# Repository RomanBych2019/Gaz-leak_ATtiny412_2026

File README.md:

# Контроллер датчика газа на ATtiny412

Назначение выводов:

- PA0: UPDI
- PA1: светодиод состояния платы
- PA2: вход АЦП датчика с внешней подтяжкой 4.7 кОм к GND
- PA3: отладочный TX, программный UART 2400 бод
- PA6: выход силового ключа 2
- PA7: выход силового ключа 1

Основная логика:

- после прогрева выполняется первоначальная калибровка чистого воздуха;
- новое значение сравнивается с сохраненным в EEPROM: если разница не больше допустимой, оно применяется и записывается; если разница большая, используется сохраненное значение;
- обрыв датчика или замыкание линии на GND определяется по АЦП около 0 В;
- замыкание выхода датчика на питание определяется по АЦП около +5 В;
- в LIN-варианте PA7 управляет BTS4142N; программная проверка замыкания нагрузки и повторные включения не выполняются;
- состояние ALARM защелкивается до перезапуска питания контроллера;
- неисправности датчика являются восстанавливаемыми.

Автокалибровку можно отключить на этапе компиляции в `src/main.cpp`:

```cpp
#define AUTOCALIBR 0
```

При отключенной автокалибровке используются фиксированные заводские пороги АЦП.

Для выбора поведения PA6/PA7 измените `SENSOR_MODIFICATION` в `src/main.cpp`.

Варианты сборки:

- `attiny412`: распиновка базовой платы;
- `attiny412_lin`: распиновка платы с LIN-драйвером, сборка с `LIN_DRIVER`.

Сборка:

```sh
pio run -e attiny412
pio run -e attiny412_lin
```

Прошивка:

Проект использует `serialupdi`. Скорость загрузки задана в `platformio.ini`:
`upload_speed = 19200`.

Обычная версия:

```sh
pio run -e attiny412 -t upload
```

LIN-версия:

```sh
pio run -e attiny412_lin -t upload
```

Если программатор не определяется автоматически, укажите порт в `platformio.ini`:

```ini
upload_port = /dev/cu.usbserial-4
```

## Ограничение LIN_DRIVER

LIN-версия занимает `3296/4096` байт flash, свободно 800 байт
при текущих настройках (`MOD_SINGLE_LOW`, `DEBUG=0`, `AUTOCALIBR=0`).
При любом повторном запросе на изменение LIN-версии необходимо до внесения
изменений предупредить оператора об ограниченном резерве flash. Если новый код
не помещается, нужно согласовать, какой существующий функционал можно удалить или
упростить.

## LIN-вариант

- трансивер: TLIN2029ADRBRQ1;
- скорость обмена: 19200 бод;

- PA0: UPDI
- PA1: LIN TXD
- PA2: LIN RXD 
- PA3: светодиод состояния платы/отладочный TX, программный UART 2400 бод
- PA6: вход АЦП датчика с внешней подтяжкой 4.7 кОм к GND
- PA7: выход управления силовым ключом BTS4142N (через R6 на вход IN)

- статусный кадр: LIN ID `0x12`, PID `0x92`, enhanced checksum;
- данные ответа: `state`, `flags`, `adc_l`, `adc_h`;
- `flags`: bit0 = ALARM защелкнут, bit1 = выход PA7 активен, bit2 = неисправность, bit3 = прогрев; биты 4–7 зарезервированы и равны 0.

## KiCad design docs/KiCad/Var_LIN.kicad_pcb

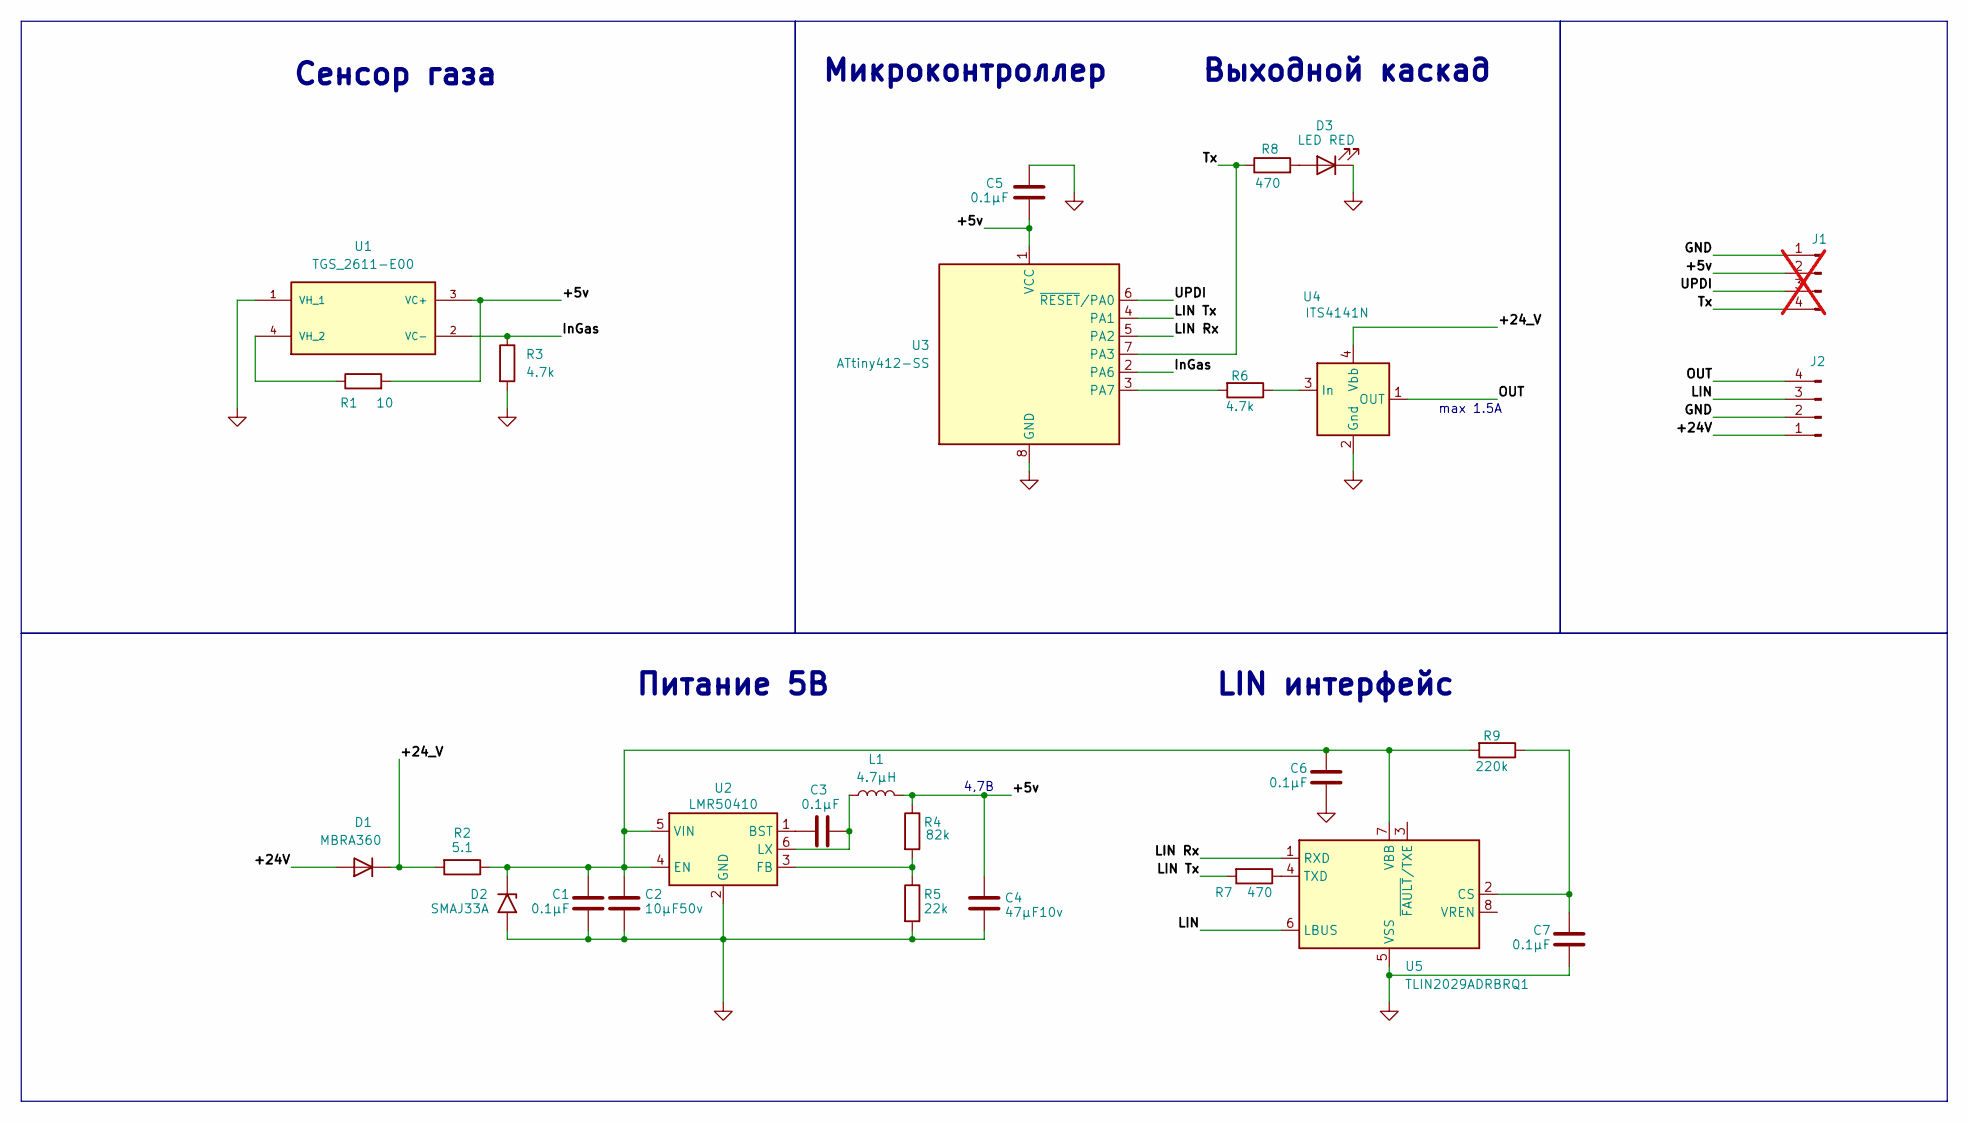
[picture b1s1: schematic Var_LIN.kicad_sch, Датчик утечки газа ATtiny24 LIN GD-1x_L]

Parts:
C1, C3, C5, C6, C7: 0.1µF; C_0603_1608Metric
C2: 10µF50v; C_0805_2012Metric
C4: 47µF10v; C_0805_2012Metric
D1: MBRA360; D_SMA
D2: SMAJ33A; D_SMA
D3: LED RED; LED_0805_2012Metric
J1: Conn_01x04_Pin; PinHeader_1x04_P1.27mm_Vertical; not fitted
J2: Conn_01x04_Pin; SSEAL_4
L1: 4.7µH; L_1210_3225Metric
R1: 10; R_0805_2012Metric
R2: 5.1; R_0805_2012Metric
R3, R6: 4.7k; R_0603_1608Metric
R4: 82k; R_0603_1608Metric
R5: 22k; R_0603_1608Metric
R7, R8: 470; R_0603_1608Metric
R9: 220k; R_0603_1608Metric
U1: TGS_2611-E00; TO180P920X780-4P; PARTREV 0718
U2: LMR50410; SOT-23-6
U3: ATtiny412-SS; SOIC-8_3.9x4.9mm_P1.27mm
U4: ITS4141N; SOT-223
U5: TLIN2029ADRBRQ1; VSON-8-1EP_3x3mm_P0.65mm_EP1.65x2.4mm

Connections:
/+5v: C4.1, C5.2, J1.2, L1.2, R1.2, R4.1, U1.3 (VC+), U3.1 (VCC)
/+24V: D1.2 (A), J2.1
/+24_V: D1.1 (K), R2.2, U4.4 (Vbb)
/InGas: R3.1, U1.2 (VC-), U3.2 (PA6)
/LIN: J2.3, U5.6 (LBUS)
/LIN Rx: U3.5 (PA2), U5.1 (RXD)
/LIN Tx: R7.2, U3.4 (PA1)
/OUT: J2.4, U4.1 (OUT), U4.5 (OUT)
/Tx: J1.4, R8.1, U3.7 (PA3)
/UPDI: J1.3, U3.6 (~RESET/PA0)
GND: C1.2, C2.2, C4.2, C5.1, C6.2, C7.2, D2.2 (A2), D3.1 (K), J1.1, J2.2, R3.2, R5.2, U1.1 (VH_1), U2.2 (GND), U3.8 (GND), U4.2 (Gnd), U5.5 (VSS)
unnamed: C1.1, C2.1, C6.1, D2.1 (A1), R2.1, R9.2, U2.4 (EN), U2.5 (VIN), U5.7 (VBB)
unnamed: D3.2 (A), R8.2
unnamed: R1.1, U1.4 (VH_2)
unnamed: C3.2, U2.1 (BST)
unnamed: R4.2, R5.1, U2.3 (FB)
unnamed: C3.1, L1.1, U2.6 (LX)
unnamed: R6.2, U3.3 (PA7)
unnamed: R6.1, U4.3 (In)
unnamed: C7.1, R9.1, U5.2 (CS)
unnamed: R7.1, U5.4 (TXD)

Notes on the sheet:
Сенсор газа
max 1.5A
4,7В
Микроконтроллер Выходной каскад
Питание 5В LIN интерфейс

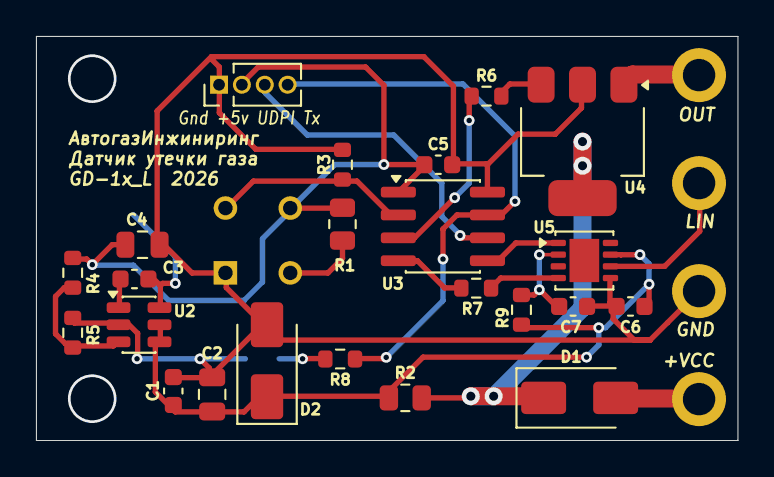
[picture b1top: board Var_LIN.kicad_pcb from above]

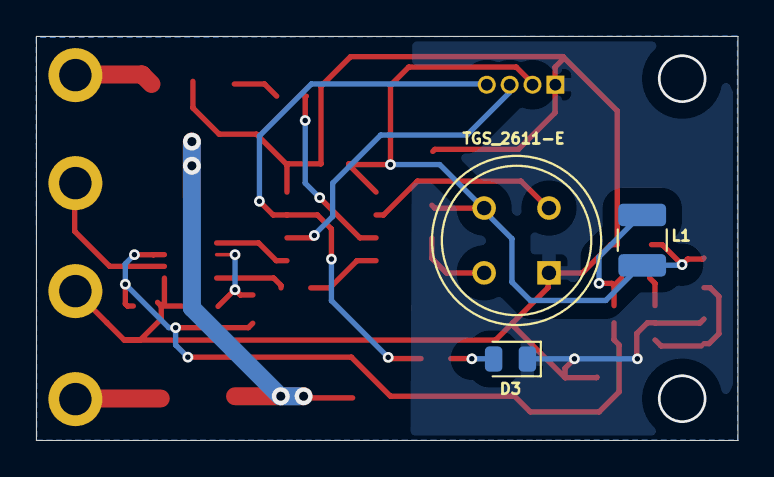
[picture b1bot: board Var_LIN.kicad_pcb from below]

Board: 2 copper layers, 39.0 x 22.4 mm, 27 parts (3 on the bottom side), 21 nets.

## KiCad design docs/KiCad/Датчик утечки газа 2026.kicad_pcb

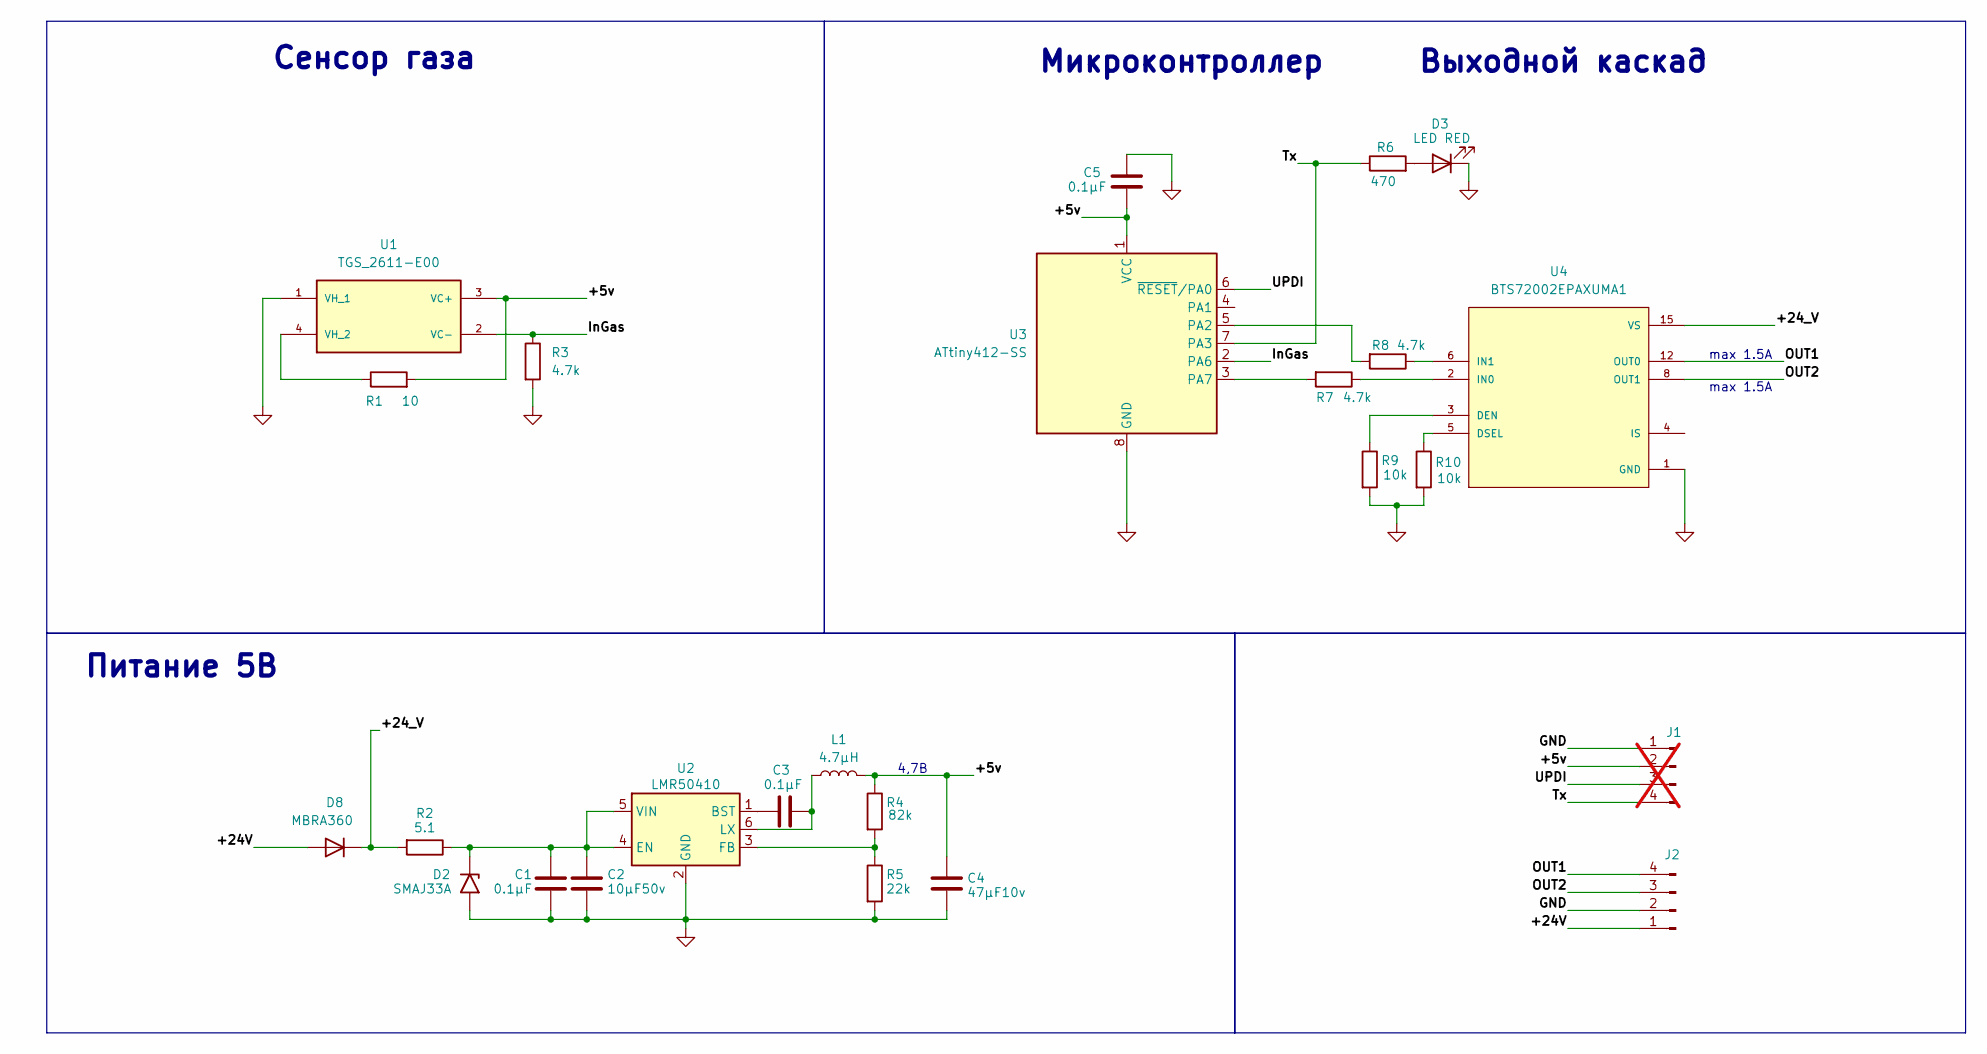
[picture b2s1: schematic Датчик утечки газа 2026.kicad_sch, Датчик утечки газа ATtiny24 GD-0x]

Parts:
C1, C3, C5: 0.1µF; C_0603_1608Metric
C2: 10µF50v; C_0805_2012Metric
C4: 47µF10v; C_0805_2012Metric
D2: SMAJ33A; D_SMA
D3: LED RED; LED_0805_2012Metric
D8: MBRA360; D_SMA
J1: Conn_01x04_Pin; PinHeader_1x04_P1.27mm_Vertical; not fitted
J2: Conn_01x04_Pin; SSEAL_4
L1: 4.7µH; L_1210_3225Metric
R1: 10; R_0805_2012Metric
R2: 5.1; R_0805_2012Metric
R3, R7, R8: 4.7k; R_0603_1608Metric
R4: 82k; R_0603_1608Metric
R5: 22k; R_0603_1608Metric
R6: 470; R_0603_1608Metric
R9, R10: 10k; R_0603_1608Metric
U1: TGS_2611-E00; TO180P920X780-4P; PARTREV 0718
U2: LMR50410; SOT-23-6
U3: ATtiny412-SS; SOIC-8_3.9x4.9mm_P1.27mm
U4: BTS72002EPAXUMA1; SOP65P600X115-15N_BTS72002EPAXUMA1; PARTREV 1.06

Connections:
/+5v: C4.1, C5.2, J1.2, L1.2, R1.2, R4.1, U1.3 (VC+), U3.1 (VCC)
/+24V: D8.2 (A), J2.1
/+24_V: D8.1 (K), R2.2, U4.15 (VS)
/InGas: R3.1, U1.2 (VC-), U3.2 (PA6)
/OUT1: J2.4, U4.12 (OUT0), U4.13 (OUT0), U4.14 (OUT0)
/OUT2: J2.3, U4.8 (OUT1), U4.9 (OUT1), U4.10 (OUT1)
/Tx: J1.4, R6.1, U3.7 (PA3)
/UPDI: J1.3, U3.6 (~RESET/PA0)
GND: C1.2, C2.2, C4.2, C5.1, D2.2 (A2), D3.1 (K), J1.1, J2.2, R3.2, R5.2, R9.2, R10.2, U1.1 (VH_1), U2.2 (GND), U3.8 (GND), U4.1 (GND)
unnamed: C1.1, C2.1, D2.1 (A1), R2.1, U2.4 (EN), U2.5 (VIN)
unnamed: D3.2 (A), R6.2
unnamed: R1.1, U1.4 (VH_2)
unnamed: C3.2, U2.1 (BST)
unnamed: R4.2, R5.1, U2.3 (FB)
unnamed: C3.1, L1.1, U2.6 (LX)
unnamed: R8.2, U3.5 (PA2)
unnamed: R7.2, U3.3 (PA7)
unnamed: R9.1, U4.3 (DEN)
unnamed: R10.1, U4.5 (DSEL)
unnamed: R7.1, U4.2 (IN0)
unnamed: R8.1, U4.6 (IN1)

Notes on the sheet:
4,7В
max 1.5A
Сенсор газа
Микроконтроллер Выходной каскад
Питание 5В

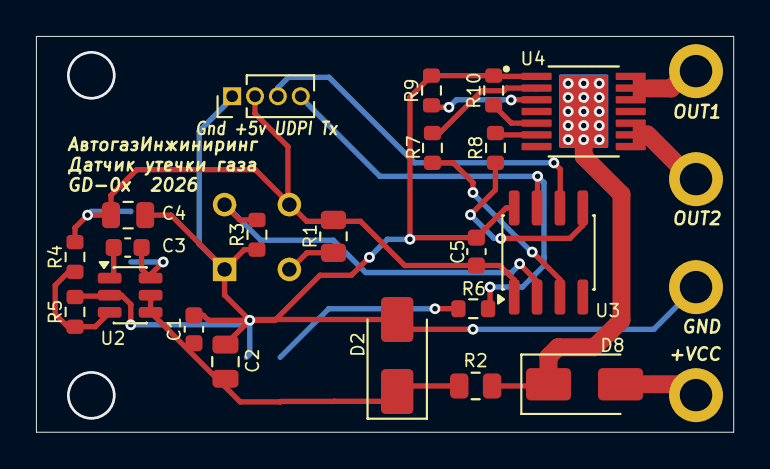
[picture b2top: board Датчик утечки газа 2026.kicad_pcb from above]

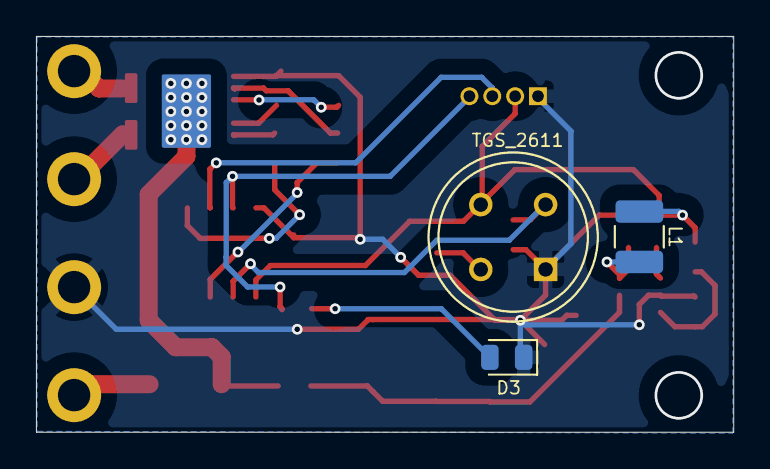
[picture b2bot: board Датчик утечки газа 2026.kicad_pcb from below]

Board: 2 copper layers, 38.7 x 22.0 mm, 25 parts (3 on the bottom side), 21 nets.

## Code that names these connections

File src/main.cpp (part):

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// ============================================================
// Контроллер датчика газа на ATtiny412
// ============================================================
// PA0 - UPDI, не использовать как GPIO
// PA1 - светодиод состояния платы                | LIN TX в версии LIN_DRIVER
// PA2 - вход АЦП датчика                         | LIN RX в версии LIN_DRIVER
// PA3 - отладочный TX, программный UART 9600 бод | светодиод состояния платы в версии LIN_DRIVER 
// PA6 - выход силового ключа 2                   | вход АЦП датчика в версии LIN_DRIVER 
// PA7 - выход силового ключа 1                   | единственный активный выход в версии LIN_DRIVER
//
// Логика:
// - напряжение датчика проверяется по заводским или откалиброванным порогам АЦП
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#endif

#if LIN_DRIVER
#define LED_PIN PIN_PA3
#define SENSOR_PIN PIN_PA6
#define DEBUG_TX_PIN PIN_PA3
#define KEY_PIN PIN_PA7
#define LIN_RX_PIN PIN_PA2
#define LIN_TX_PIN PIN_PA1
#else
#define LED_PIN PIN_PA1
#define SENSOR_PIN PIN_PA2
#define DEBUG_TX_PIN PIN_PA3
#define KEY1_PIN PIN_PA7
#define KEY2_PIN PIN_PA6
#endif

#if DEBUG && LIN_DRIVER
// В LIN-версии PA3 используется светодиодом, но при DEBUG приоритет у
// отладочного TX на PA3, поэтому индикация светодиодом отключается.
#define LED_ENABLED 0
#else
#define LED_ENABLED 1
#endif

// ============================================================
// Отладочный программный UART на PA3
// ============================================================

#if DEBUG
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//
// TLIN2029ADRBRQ1 - это физический LIN-трансивер. Протокол LIN
// обслуживает ATtiny412 через USART0:
// - TXD трансивера <- PA1 / LIN_TX_PIN
// - RXD трансивера -> PA2 / LIN_RX_PIN
//
// Узел работает как LIN slave и отвечает на header с PID 0x92
// (LIN ID 0x12) статусным кадром:
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#if !LIN_DRIVER

// ============================================================
// Варианты поведения PA6 / PA7
// ============================================================
//
// MOD_SINGLE_HIGH:
//   NORMAL       PA6=0, PA7=0
//   ALARM        PA6=0, PA7=1
//
// MOD_SINGLE_LOW:
//   NORMAL       PA6=0, PA7=1
//   ALARM        PA6=0, PA7=0
//
// MOD_DUAL_HIGH:
//   NORMAL       PA6=0, PA7=0
//   ALARM        PA6=1, PA7=1
//
// MOD_COMPLEMENTARY:
//   NORMAL       PA6=1, PA7=0
//   ALARM        PA6=0, PA7=1
//
// MOD_ACTIVE_LOW:
//   NORMAL       PA6=1, PA7=1
//   ALARM        PA6=0, PA7=0
//
// Во время WARMUP PA6/PA7 в NORMAL.

enum SensorModification {
  MOD_SINGLE_HIGH, // ключ OUT1 с активным высоким уровнем, высокий уровень на
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#else

// ============================================================
// Варианты поведения PA7
// ============================================================
//
// MOD_SINGLE_HIGH:
//   NORMAL       PA7=0
//   ALARM        PA7=1
//
// MOD_SINGLE_LOW:
//   NORMAL       PA7=1
//   ALARM        PA7=0
//
//

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// Индикация светодиодом
// ============================================================
//
// В базовой версии светодиод на PA1. В LIN-версии светодиод на PA3,
// но при DEBUG он отключается, потому что PA3 используется как отладочный TX.
//
// WARMUP              - короткая вспышка раз в секунду
// NORMAL              - короткая вспышка раз в 2 секунды
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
